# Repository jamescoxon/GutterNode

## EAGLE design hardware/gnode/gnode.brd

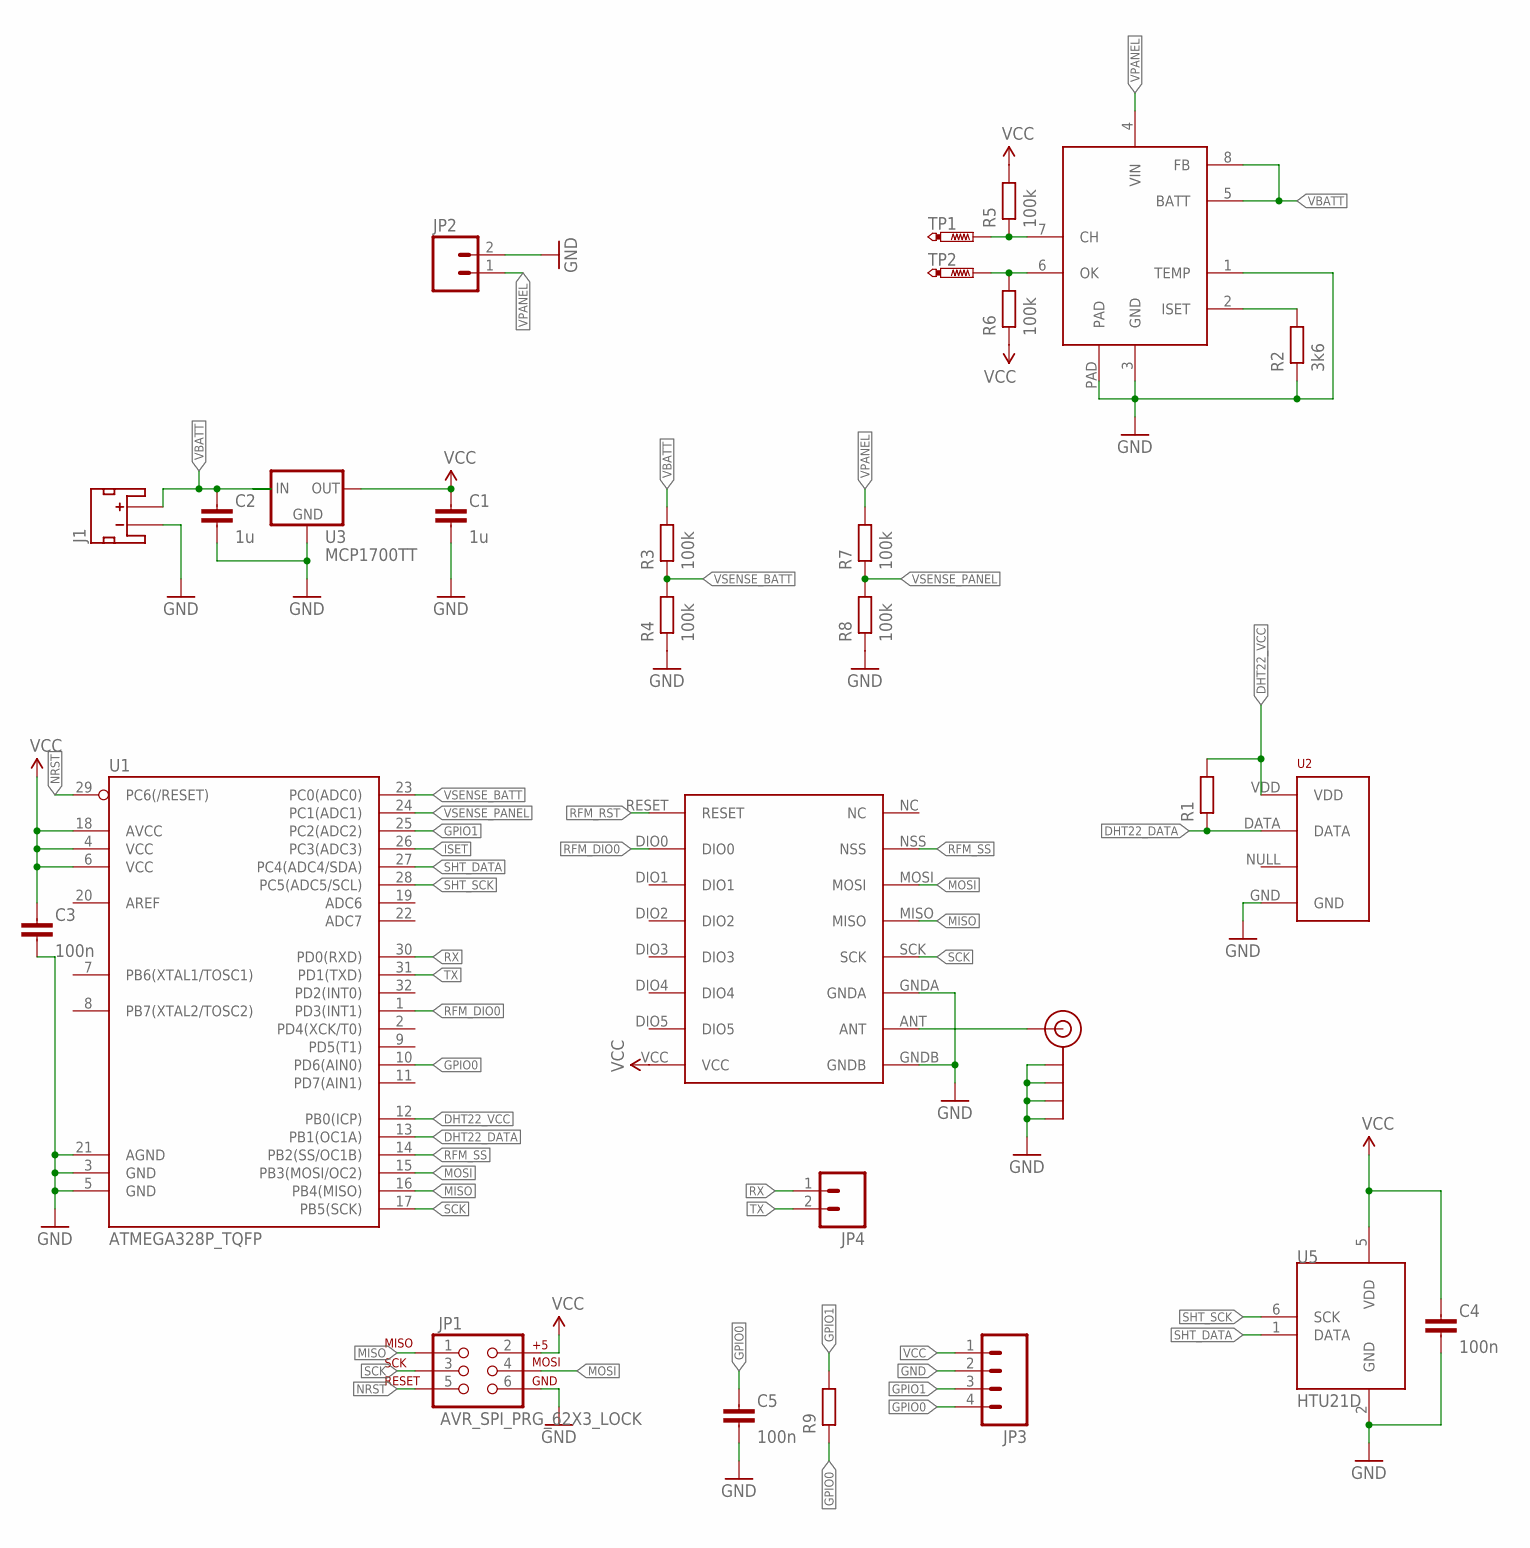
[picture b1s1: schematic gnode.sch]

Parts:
C1, C2: 1u; C0603-N
C3, C4, C5: 100n; C0603-N
J1: JST_2MM_MALE_TH; JST-2-TH
J$1: SMA_EDGE; SMA-EDGE
JP1: AVR_SPI_PRG_62X3_LOCK; 2X3_LOCK
JP2, JP4: M02PTH; 1X02
JP3: M04PTH; 1X04
R1, R9: RESISTOR0603-N; R0603-N
R2: 3k6; R0603-N
R3, R4, R5, R6, R7, R8: 100k; R0603-N
TP1, TP2: PTR1B1,27; B1,27
U1: ATMEGA328P_TQFP; TQFP32-08
U2: RHT03_DHT-22_AM2302; RHT03_DHT-22
U3: MCP1700TT; SOT23
U4: CN3083; SO8-PAD
U5: HTU21D; DFN6-L
U$1: RFM69HW; RFM

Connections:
DHT22_DATA: R1.1, U1.13 (PB1(OC1A)), U2.DATA
DHT22_VCC: R1.2, U1.12 (PB0(ICP)), U2.VDD
GND: C1.2, C2.2, C3.2, C4.2, C5.2, J1.2 (-), J$1.GND@0 (GND), J$1.GND@1 (GND), J$1.GND@2 (GND), J$1.GND@3 (GND), JP1.6, JP2.2, JP3.2, R2.1, R4.1, R8.1, U1.3 (GND), U1.5 (GND), U1.21 (AGND), U2.GND, U3.1 (GND), U4.1 (TEMP), U4.3 (GND), U4.PAD, U5.2 (GND), U$1.GNDA, U$1.GNDB
GPIO0: C5.1, JP3.4, R9.1, U1.10 (PD6(AIN0))
GPIO1: JP3.3, R9.2, U1.25 (PC2(ADC2))
ISET: R2.2, U1.26 (PC3(ADC3)), U4.2 (ISET)
MISO: JP1.1, U1.16 (PB4(MISO)), U$1.MISO
MOSI: JP1.4, U1.15 (PB3(MOSI/OC2)), U$1.MOSI
unnamed: J$1.SIG (SIGNAL), U$1.ANT
unnamed: R5.1, TP1.TP, U4.7 (CH)
unnamed: R6.2, TP2.TP, U4.6 (OK)
NRST: JP1.5, U1.29 (PC6(/RESET))
RFM_DIO0: U1.1 (PD3(INT1)), U$1.DIO0
RFM_RST: U$1.RESET
RFM_SS: U1.14 (PB2(SS/OC1B)), U$1.NSS
RX: JP4.1, U1.30 (PD0(RXD))
SCK: JP1.3, U1.17 (PB5(SCK)), U$1.SCK
SHT_DATA: U1.27 (PC4(ADC4/SDA)), U5.1 (DATA)
SHT_SCK: U1.28 (PC5(ADC5/SCL)), U5.6 (SCK)
TX: JP4.2, U1.31 (PD1(TXD))
VBATT: C2.1, J1.1 (+), R3.2, U3.3 (IN), U4.5 (BATT), U4.8 (FB)
VCC: C1.1, C3.1, C4.1, JP1.2, JP3.1, R5.2, R6.1, U1.4 (VCC), U1.6 (VCC), U1.18 (AVCC), U3.2 (OUT), U5.5 (VDD), U$1.VCC
VPANEL: JP2.1, R7.2, U4.4 (VIN)
VSENSE_BATT: R3.1, R4.2, U1.23 (PC0(ADC0))
VSENSE_PANEL: R7.1, R8.2, U1.24 (PC1(ADC1))

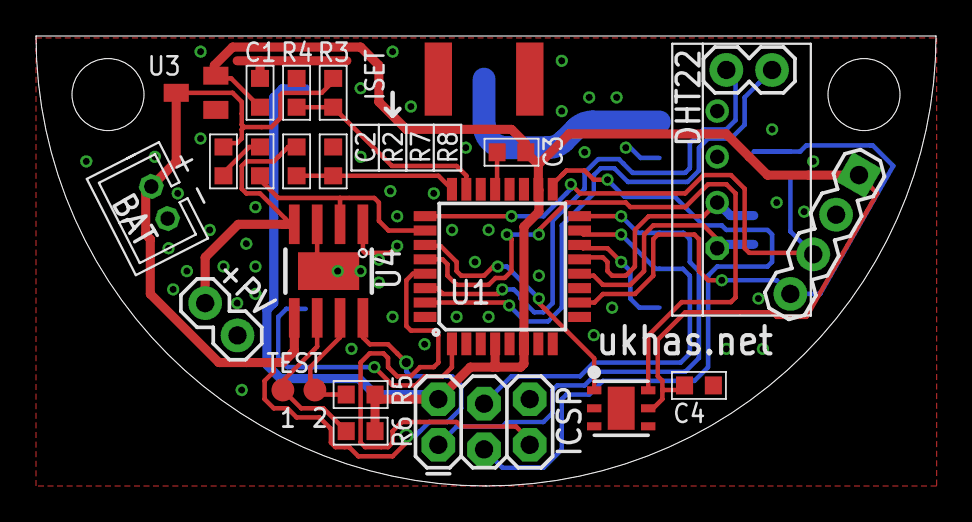
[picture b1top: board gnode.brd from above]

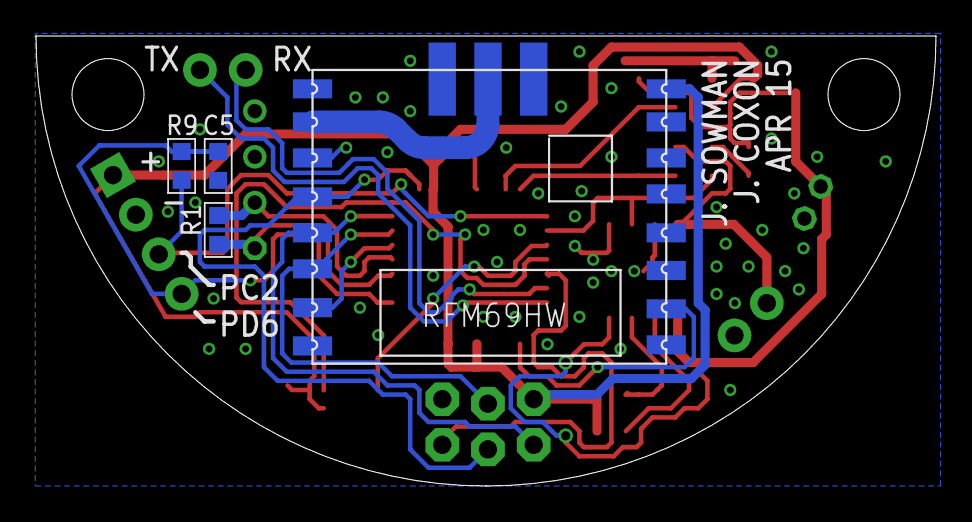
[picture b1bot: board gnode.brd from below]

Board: 2 copper layers, 50.0 x 25.0 mm, 28 parts (5 on the bottom side), 24 nets.

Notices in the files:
parts and their libraries:
SparkFun-DigitalIC: Licensing: Creative Commons ShareAlike 4.0 International - https://creativecommons.org/licenses/by-sa/4.0
